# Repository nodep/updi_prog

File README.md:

# updi_prog
UPDI programmer for AVR microcontrollers based on FT232RL

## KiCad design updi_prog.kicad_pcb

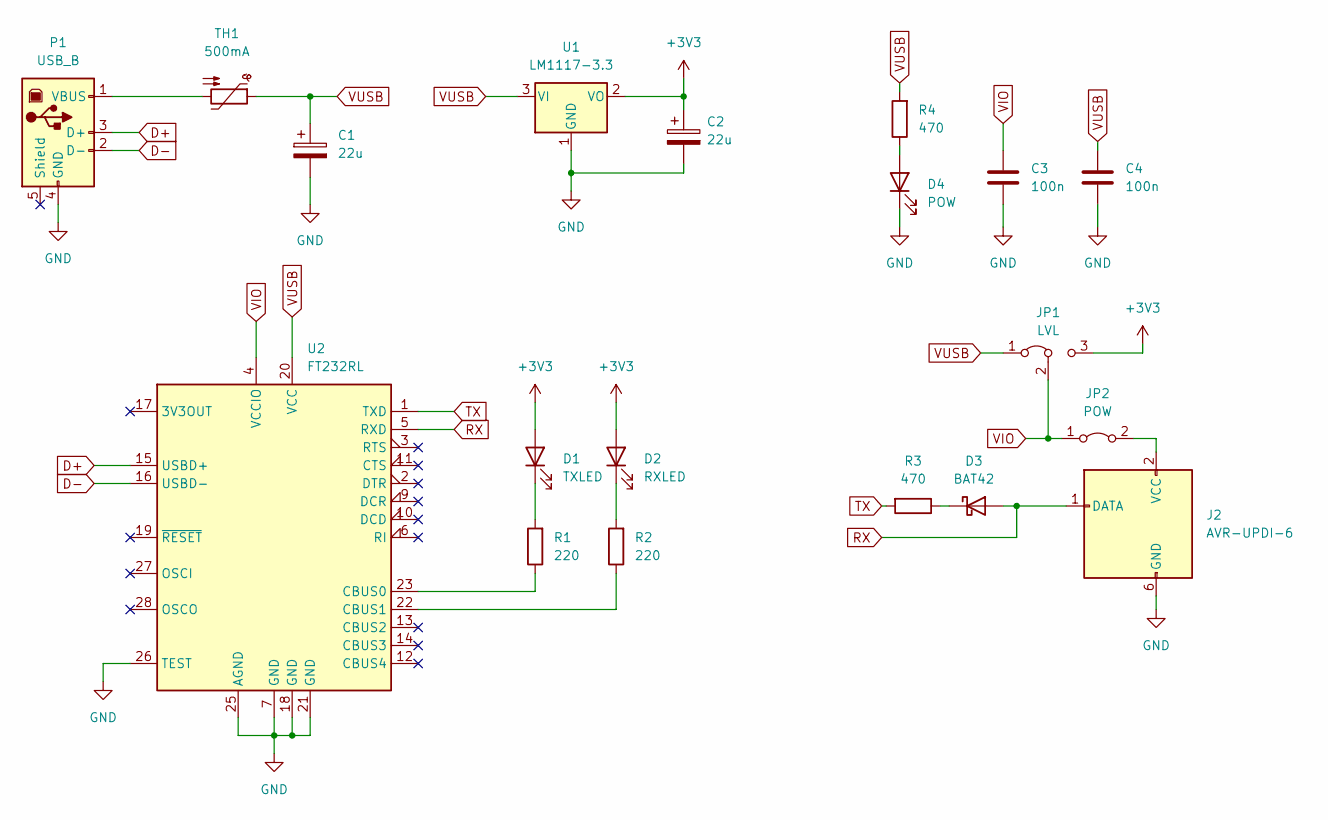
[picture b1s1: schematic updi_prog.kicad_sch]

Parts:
C1, C2: 22u; CP_Radial_D5.0mm_P2.50mm
C3, C4: 100n; C_1206_3216Metric_Pad1.33x1.80mm_HandSolder
D1: TXLED; LED_D3.0mm_Clear
D2: RXLED; LED_D3.0mm_Clear
D3: BAT42; D_DO-35_SOD27_P7.62mm_Horizontal
D4: POW; LED_D3.0mm_Clear
J2: AVR-UPDI-6; PinHeader_2x03_P2.54mm_Vertical
JP1: LVL; PinHeader_1x03_P2.54mm_Vertical
JP2: POW; PinHeader_1x02_P2.54mm_Vertical
P1: USB_B; USB_B_Lumberg_2411_02_Horizontal
R1, R2: 220; R_1206_3216Metric_Pad1.30x1.75mm_HandSolder
R3, R4: 470; R_1206_3216Metric_Pad1.30x1.75mm_HandSolder
TH1: 500mA; Fuse_1206_3216Metric_Pad1.42x1.75mm_HandSolder
U1: LM1117-3.3; SOT-223-3_TabPin2
U2: FT232RL; SSOP-28_5.3x10.2mm_P0.65mm

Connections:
+3V3: C2.1, D1.2 (A), D2.2 (A), JP1.3 (B), U1.2 (VO)
D+: P1.3 (D+), U2.15 (USBD+)
D-: P1.2 (D-), U2.16 (USBD-)
GND: C1.2, C2.2, C3.2, C4.2, D4.1 (K), J2.6 (GND), P1.4 (GND), U1.1 (GND), U2.7 (GND), U2.18 (GND), U2.21 (GND), U2.25 (AGND), U2.26 (TEST)
unnamed: D1.1 (K), R1.2
unnamed: D2.1 (K), R2.2
unnamed: D3.1 (K), R3.1
unnamed: D4.2 (A), R4.1
unnamed: J2.2 (VCC), JP2.2 (B)
unnamed: P1.1 (VBUS), TH1.2
unnamed: R1.1, U2.23 (CBUS0)
unnamed: R2.1, U2.22 (CBUS1)
RX: D3.2 (A), J2.1 (DATA), U2.5 (RXD)
TX: R3.2, U2.1 (TXD)
VIO: C3.1, JP1.2 (C), JP2.1 (A), U2.4 (VCCIO)
VUSB: C1.1, C4.1, JP1.1 (A), R4.2, TH1.1, U1.3 (VI), U2.20 (VCC)

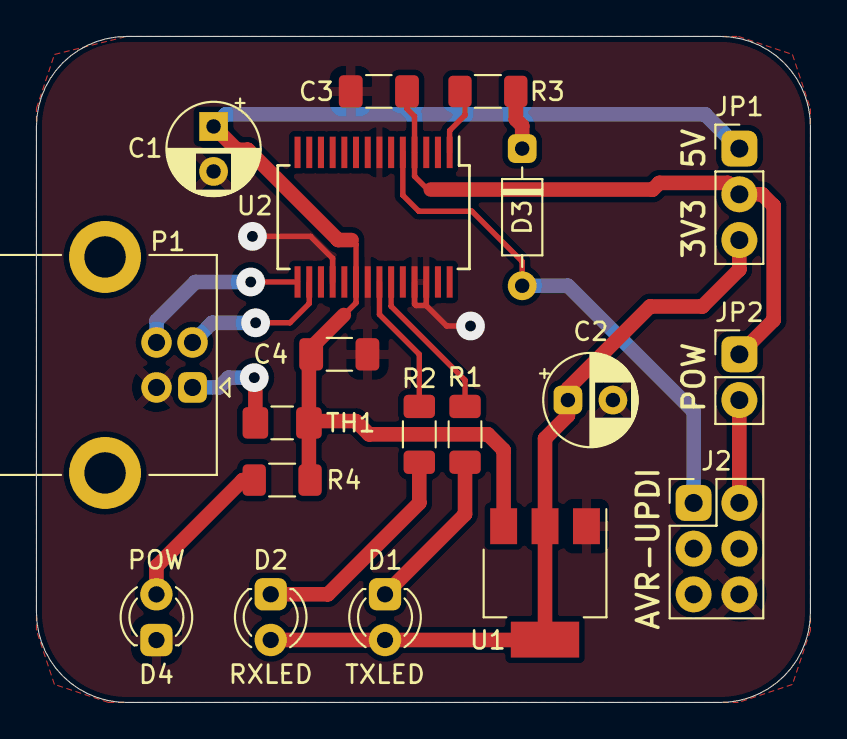
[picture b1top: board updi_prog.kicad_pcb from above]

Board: 2 copper layers, 43.0 x 37.0 mm, 19 parts (0 on the bottom side), 16 nets.

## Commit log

2022-03-10 inital commit
2022-03-10 kicad_prl is not needed
2022-03-10 added power led
2022-03-12 smaller pcb
2022-03-15 changed connector to standard AVR-UPDI
